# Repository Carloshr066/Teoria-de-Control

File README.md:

# Teoria-de-Control

Repositorio de github para el proyecto del pendulo invertido de la asignatura de Teoria de control. Tambien incluye las librerias de los PIDs de las prácticas de tiempo discreto.

## Estructura de archivos
- Pendulo_inv.ino: Codigo principal del pendulo invertido.
- Calibrate_sensor.ino: Codigo para calibrar el sensor del pendulo invertido.
- Archivos_diseño_pendulo: Carpeta que contiene los archivos de diseño del pendulo, tanto la PCB y esquema electrico como el modelo 3d del chasis.
- Librerias_PIDs: Carpeta que contiene los archivos de las librerias que implementan los distintos tipos de PIDs de tiempo discreto.

## Metodología seguida
- Selección de los componentes eléctricos y mecánicos para el proyecto
 
- Diseño del esquema electrico y PCB, seguiendo el esquema de conexiones de los componentes.

- Diseño del chasis en base a los componentes elegidos y la PCB diseñada.
 
- Montaje y prueba de los componentes en la PCB fabricada.
 
- Implementación del codigo inicial en la ESP32.
 
- Ajuste del codigo para su correcto funcionamiento.

## Componentes:

  - Esp32 devkit:
    Como parte central del pendulo se ha usado una Esp32 devkit para controlar el pendulo.
    
  - ROB-14450:
    Puente H capaz de controlar 2 motores DC a la vez, permite un voltaje de alimentación de hasta 15v.
    
  - SEN0142:
    Sensor con giroscopio y acelerometro incorporado, usado para medir el angulo del robot y corregirlo.
    
  - LM7805CT/NOPB:
    Transistor para regular el voltaje, tiene un voltaje de salida de 5V perfecto para alimentar la Esp32 devkit y permite hasta 35V de entrada.
    
  - Conectores XT30:
    Se han usado tres pares de conectores XT30 para conectar tanto la batería como los motores la placa.
    
  - Motores DC:
    Para mover el robot se han usado dos motores DC con un tren de engranajes reductor para incrementar el torque.
    
  - Ruedas:
    Se han usado un par de ruedas compatibles con el eje de los motores.
    
  - Batería:
    Se ha usado una batería recargable de 6V para todo el robot.
## Chasis:
El chasis se ha diseñado con la intención de tener un centro de gravedad alineado con el eje de los motores para maximizar la establidad del robot. El chasis en si es muy sencillo, una superficie plana con 4 agujeros para atornillar la placa al chasis y 2 ranuras en los laterales para poner los motores.

## Montaje:
El montaje de robot del robot ha sido principalmente soldar los componentes en la PCB, una vez esta esta lista se han usado unos separadores para que la placa quede separada una cierta distancia del chasis, espacio en el que se ha puesto la batería para tener un perfil más bajo. Con la placa y la batería puestas solo falta colocar los motores en cada estremo del chasis y ponerles las ruedas.

## Ajuste del PID:
La constante Kp del PID se ha ido subiendo en pequeños incrementos hasta que se el robot ha sido capaz de levantarse por su cuenta. Debido a la estabilidad de base del robot poco más ha sido necesario. La constante Ki se ha incrementado hasta que el robot erá capaz de eliminar el pequeño error residual al encontrarse casi perpendicular a la superficie. La constante Kd se incremento muy ligeramente para aumentar la velocidad de respuesta del robot.

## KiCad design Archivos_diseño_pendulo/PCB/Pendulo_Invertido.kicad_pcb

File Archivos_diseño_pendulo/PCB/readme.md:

# Archivos de diseño de la PCB
Incluye:
- El archivo del esquema eléctrico
- El archivo del diseño de la pcb
- Los ficheros gerber y de taladrado

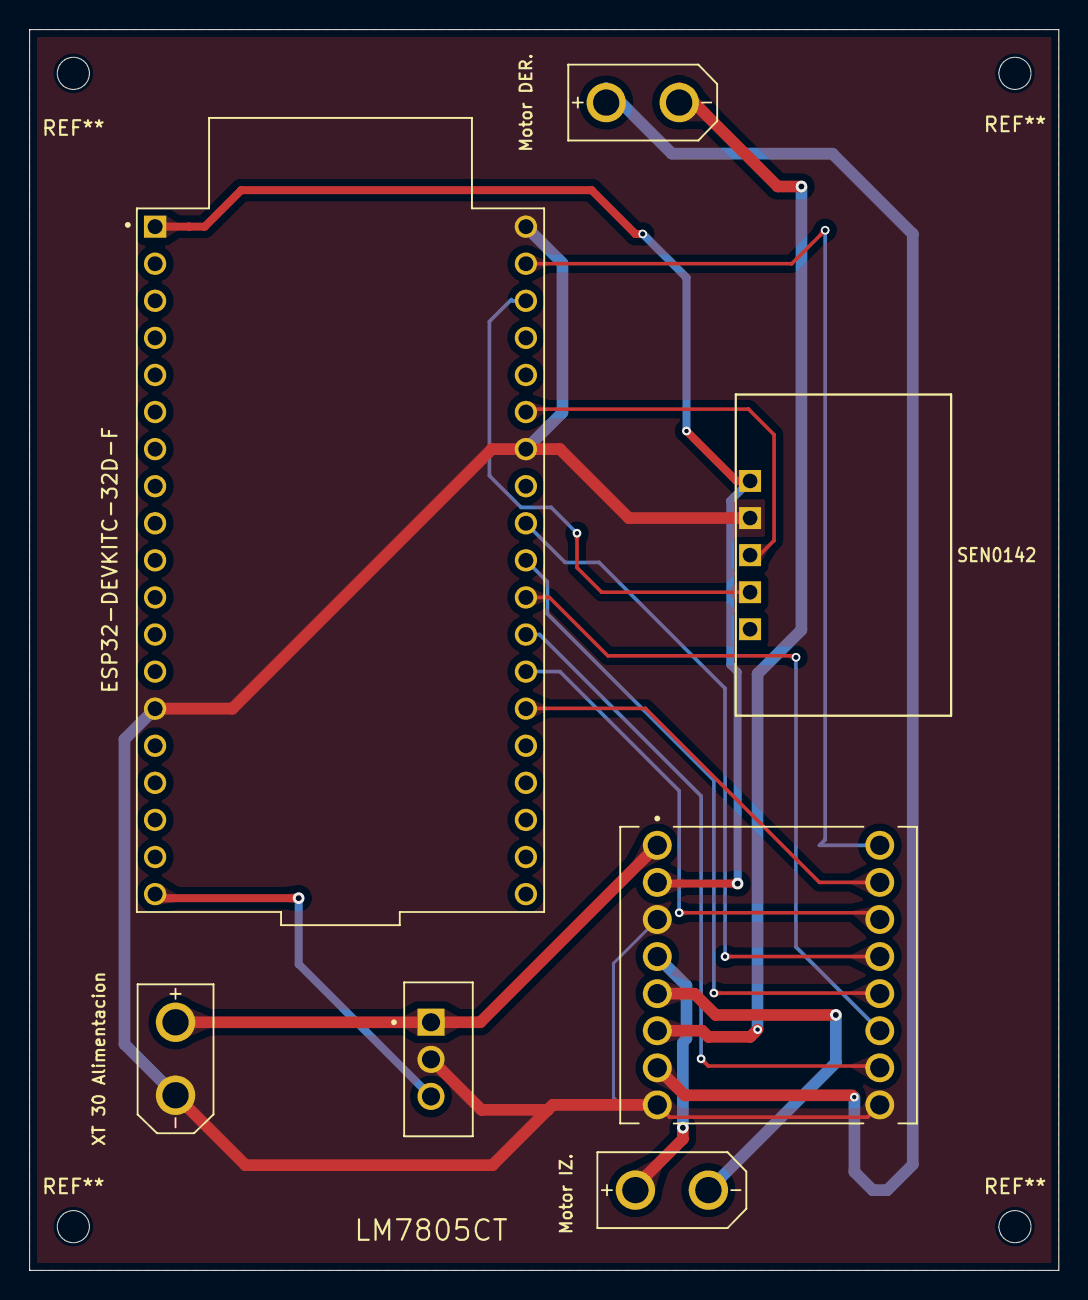
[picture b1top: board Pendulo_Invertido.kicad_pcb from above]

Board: 2 copper layers, 70.5 x 85.0 mm, 7 parts (0 on the bottom side), 17 nets.

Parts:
ESP32-DEVKITC-32D-F: ESP32-DEVKITC; MODULE_ESP32-DEVKITC
LM7805CT: LM7805CT_NOPB; TO254P1054X470X1955-3
Motor DER.: XT30UPB-M
Motor IZ.: XT30UPB-M
ROB-1445: ROB-14450; MODULE_ROB-14450
SEN0142: SEN0142
XT 30 Alimentacion: XT30UPB-M

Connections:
+3.3V: ESP32-DEVKITC-32D-F.1 (3V3), ROB-1445.2 (VCC), SEN0142.1 (VIN)
+5V: ESP32-DEVKITC-32D-F.19 (EXT_5V), LM7805CT.3 (OUT)
+6V: LM7805CT.1 (IN), ROB-1445.1 (VM), XT 30 Alimentacion.P$1 (+)
GND: ESP32-DEVKITC-32D-F.14 (GND1), ESP32-DEVKITC-32D-F.32 (GND2), ESP32-DEVKITC-32D-F.38 (GND3), LM7805CT.2 (GND), ROB-1445.3 (GND), ROB-1445.8 (GND), ROB-1445.9 (GND), SEN0142.2 (GND), XT 30 Alimentacion.P$2 (-)
unnamed: ESP32-DEVKITC-32D-F.36 (IO22), SEN0142.4 (SCL)
unnamed: ESP32-DEVKITC-32D-F.33 (IO21), SEN0142.3 (SDA)
unnamed: ESP32-DEVKITC-32D-F.25 (IO0), ROB-1445.15 (AI2)
unnamed: ESP32-DEVKITC-32D-F.26 (IO4), ROB-1445.14 (AI1)
unnamed: ESP32-DEVKITC-32D-F.29 (IO5), ROB-1445.12 (BI1)
unnamed: ESP32-DEVKITC-32D-F.27 (IO16), ROB-1445.10 (PWMB)
unnamed: ESP32-DEVKITC-32D-F.28 (IO17), ROB-1445.11 (BI2)
unnamed: ESP32-DEVKITC-32D-F.30 (IO18), ROB-1445.13 (STBY)
unnamed: ESP32-DEVKITC-32D-F.37 (IO23), ROB-1445.16 (PWMA)
unnamed: Motor IZ..P$1 (+), ROB-1445.4 (A01)
unnamed: Motor IZ..P$2 (-), ROB-1445.5 (A02)
unnamed: Motor DER..P$1 (+), ROB-1445.7 (B01)
unnamed: Motor DER..P$2 (-), ROB-1445.6 (B02)

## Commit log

2025-05-25 Create Librerias_PIDs
